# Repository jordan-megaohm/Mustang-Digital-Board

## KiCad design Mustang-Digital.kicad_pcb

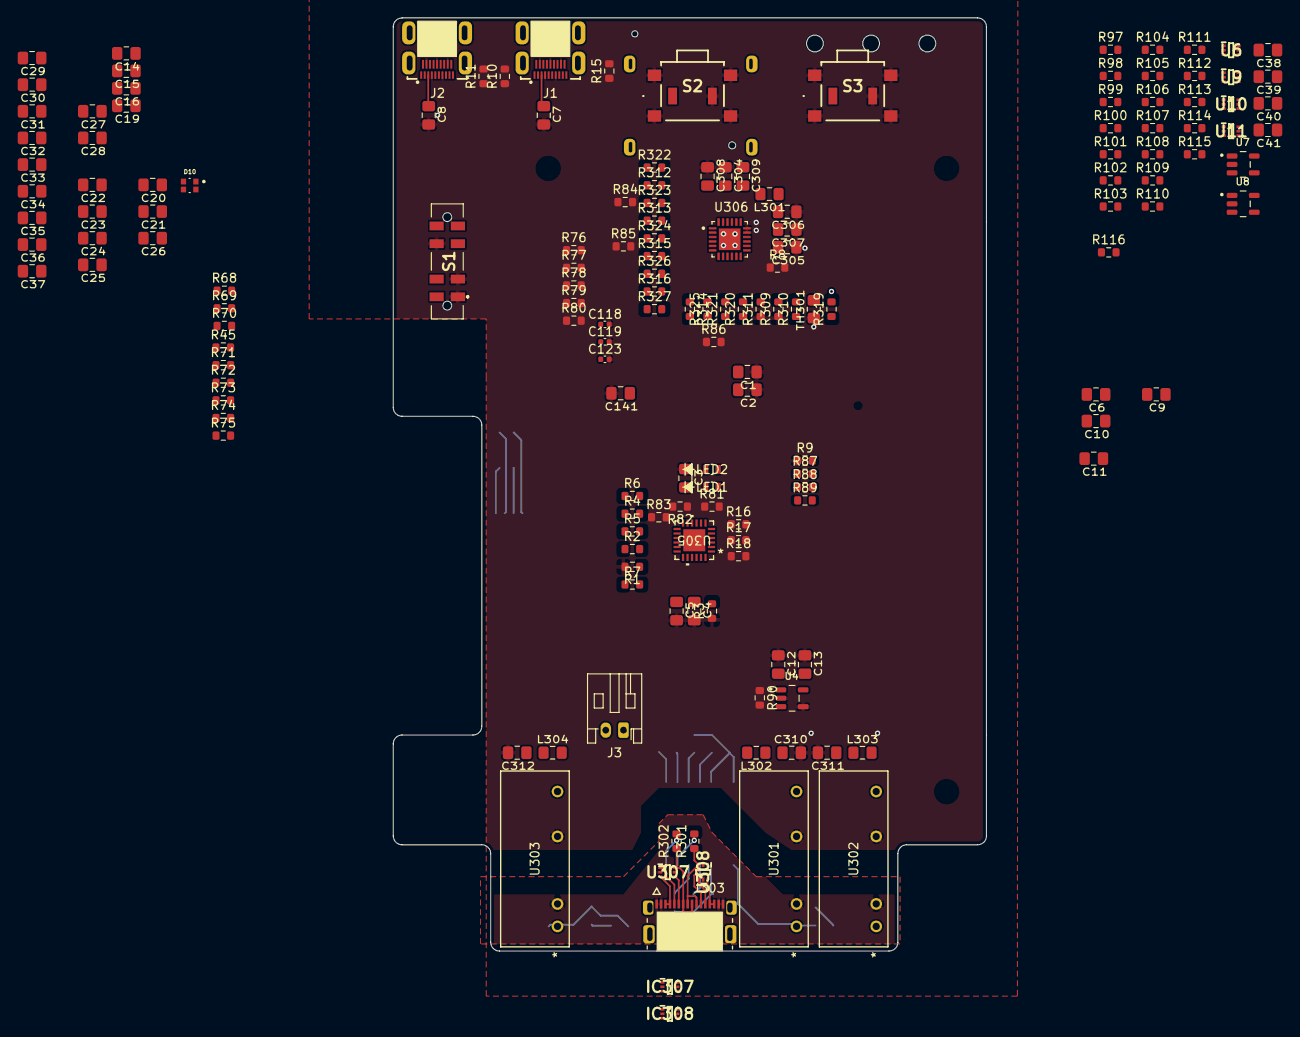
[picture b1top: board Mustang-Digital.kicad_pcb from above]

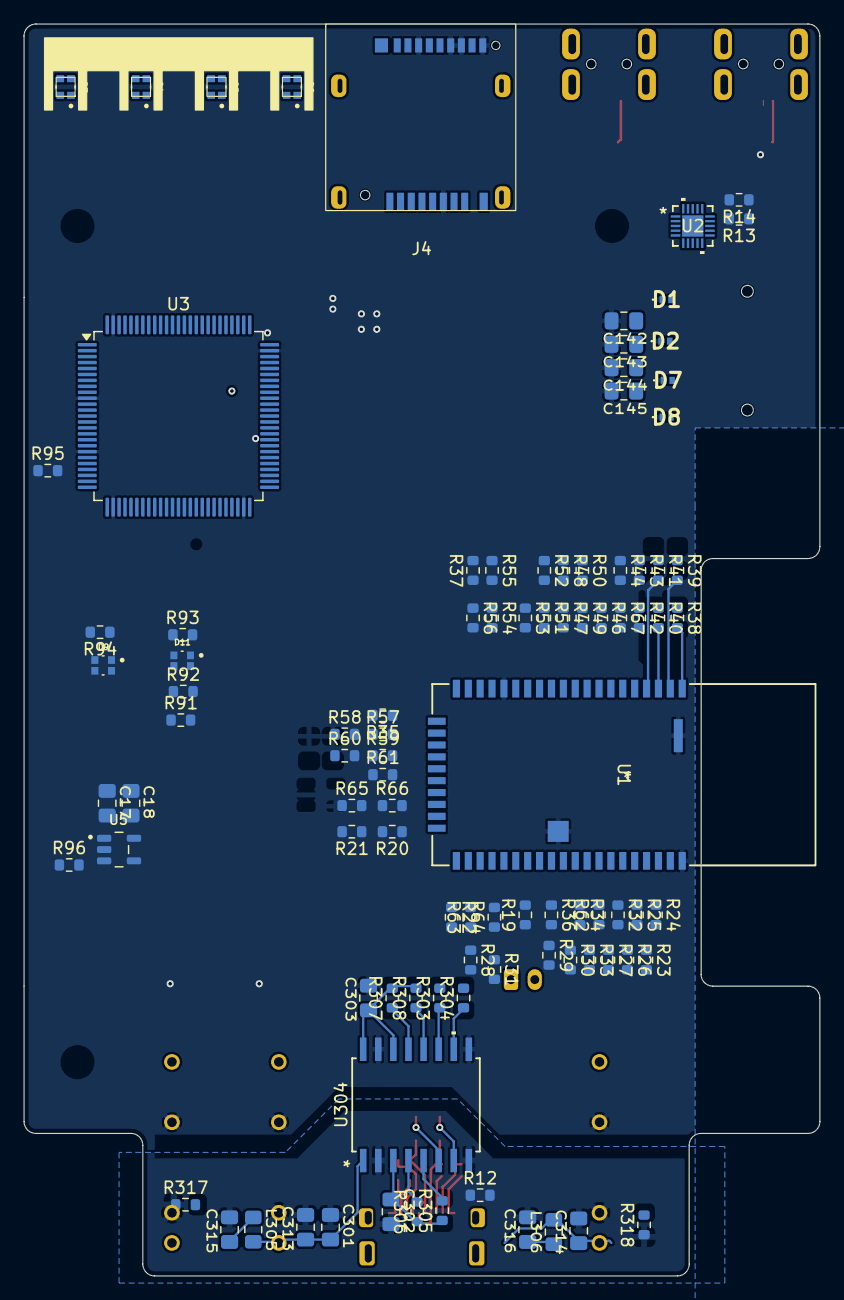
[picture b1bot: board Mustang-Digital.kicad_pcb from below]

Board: 4 copper layers, 67.0 x 105.4 mm, 258 parts (97 on the bottom side), 215 nets.

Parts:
C1, C6, C7, C8, C9, C10, C11, C20, C21, C22, C23, C24, C25, C26, C27, C28, C29, C30, C31, C32, C33, C34, C35, C36, C301, C302, C303, C315, C316: 0.1uF; C_0805_2012Metric_Pad1.18x1.45mm_HandSolder
C2, C3, C12, C13, C17, C18, C37, C38, C39, C40, C41, C143: 1uF; C_0805_2012Metric_Pad1.18x1.45mm_HandSolder
C4, C5: 18pF; C_0805_2012Metric_Pad1.18x1.45mm_HandSolder
C14, C19, C141, C142, C144, C145: .1uF; C_0805_2012Metric_Pad1.18x1.45mm_HandSolder
C15, C16: 10nF; C_0805_2012Metric_Pad1.18x1.45mm_HandSolder
C118: .1uF; C_0402_1005Metric
C119: 10nF; C_0402_1005Metric
C123: 1uF; C_0402_1005Metric
C304, C310, C311, C312, C313, C314: 4.7uF; C_0805_2012Metric_Pad1.18x1.45mm_HandSolder
C305, C306, C307: 10uF; C_0805_2012Metric_Pad1.18x1.45mm_HandSolder
C308: 8.2uF; C_0805_2012Metric_Pad1.18x1.45mm_HandSolder
C309: 47nF; C_0805_2012Metric_Pad1.18x1.45mm_HandSolder
D1, D2, D7, D8: ESD7551N2T5G
D3, D4, D5, D6, D9, D10, D11: EAST1616RGBA3; LED_EAST1616RGBA3
IC307, IC308: TPD4E1B06DRLR; SOTFL50P160X60-6N
J1, J2: 685119248123
J3: Conn_01x02_Pin_JST-PH_Batt; JST_PH_S2B-PH-K_1x02_P2.00mm_Horizontal
J4: Micro_SD_Card_4.0_CUI; microSD_XC_CUI_MSD4-1-A
J303: 2130830005; MOLEX_2130830005
L301, L305, L306: 1uH; L_0805_2012Metric_Pad1.15x1.40mm_HandSolder
L302, L303, L304: 10uH; L_0805_2012Metric_Pad1.15x1.40mm_HandSolder
LED1, LED2: EAST16084BA8; LED_EAST16084BA8_EVE
MECH1: Light_Pipe_LEDs
R1, R2: 100K; R_0603_1608Metric
R3: 12K; R_0603_1608Metric
R4, R5, R6, R7, R16, R17, R18, R19, R20, R21, R22, R23, R24, R25, R26, R27, R28, R29, R30, R31, R32, R33, R34, R35, R36, R37, R38, R39, R40, R41, R42, R47, R48, R54, R55, R56, R60, R61, R62, R70, R81, R82, R83, R90, R96, R97, R98, R99, R100, R101, R102, R103, R104, R105, R106, R107, R108, R109, R110, R111, R112, R113, R114, R115, R301, R302, R303, R304, R319, R320, R321, R322, R323, R324, R325, R326, R327: 24R; R_0603_1608Metric
R8, R9, R10, R11, R12, R13, R14, R15, R43, R44, R46, R49, R50, R51, R52, R53, R57, R58, R59, R63, R64, R65, R66, R67, R68, R69, R87, R88, R89, R95, R116: 0R; R_0603_1608Metric
R45, R72, R77, R79: 1K; R_0603_1608Metric
R71, R73, R74, R75, R78, R80, R94, R305, R306, R307, R308, R312, R313, R314, R315, R316: 10K; R_0603_1608Metric
R76: 2.7K; R_0603_1608Metric
R84, R85, R86, R91, R92, R93, R310, R317, R318: 5.23K; R_0603_1608Metric
R309: 30.9K; R_0603_1608Metric
R311: 249R; R_0603_1608Metric
S1: JS207011JCQNR
S2, S3: PTS645VN13SMTR92LFS
TH301: Thermistor; R_0805_2012Metric_Pad1.20x1.40mm_HandSolder
U1: BM83SM1-00TB; BM83_MCH
U2: LP5012RUKR; QFN_2RUKR_TEX
U3: STM32L496VGT6_Mustang; LQFP-100_14x14mm_P0.5mm
U4, U5, U7: LP5907MFX-3.3_NOPB; SOT95P280X145-5N
U6, U9, U10, U11, U307, U308: TPD4E1B06DRLR; SOTFL50P160X60-6N
U8: LP5907MFX-1.8_NOPB; SOT95P280X145-5N
U301, U302, U303: SPU03L-05; SPU03L-05_MWU
U304: ADUM4160BRWZ; RW_16_ADI
U305: USB2422T-I/MJ; SQFN24_4X4MC_MCH
U306: BQ24296RGER; QFN50P400X400X100-25N

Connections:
+3V3: C1.1, C2.1, C9.1, C13.1, C21.1, C22.1, C23.1, C24.1, C25.1, C31.1, C32.1, C33.1, C34.1, C35.1, D3.3, D4.3, D5.3, D6.3, D10.3, R69.1, R71.2, R73.2, R74.2, R75.2, R78.2, R80.2, R88.2, R89.2, R95.1, U2.16 (VCC), U3.11 (VDD), U3.28 (VDD), U3.50 (VDD), U3.75 (VDD), U3.100 (VDD), U4.5 (OUT), U305.1 (VDD33), U305.9 (VDD33), U305.18 (VDD33)
+5V: C118.1, C119.1, C123.1
/BT/P2_3: R34.2, R93.2
/BT/P2_6: R35.2, R92.2
/BT/P2_7: R36.2, R91.2
/BT/SYS_PWR: C27.1, D9.3, LED1.2, LED2.2, R59.1
/BT/USB_DM: R18.2, U1.36 (DM)
/BT/USB_DP: R19.2, U1.37 (DP)
/Buds/ENABLE_PINS: J1.18 (ENABLE_PINS), J2.18 (ENABLE_PINS)
/Buds/I2C_SCL: J1.11 (I2C_SCL), J2.11 (I2C_SCL)
/Buds/I2C_SDA: J1.9 (I2C_SDA), J2.9 (I2C_SDA)
/Buds/REF: J1.3 (REF), J2.3 (REF)
/Charging_Isolation/VBUS0: IC307.3 (IO2), IC308.6 (IO4)
/Charging_USB/5V: C6.1, C310.2, C311.2, C312.2, L302.2, L303.2, L304.2, R2.1, R57.1, R87.2, U306.1 (VBUS), U306.24 (VBUS)
/Charging_USB/BAT: C305.1, R8.1, R68.1, U306.13 (BAT), U306.14 (BAT)
/Charging_USB/BAT_INT: R86.1, R325.1
/Charging_USB/BAT_PG: R84.1, R323.1
/Charging_USB/BAT_STAT: R85.1, R324.1
/Charging_USB/BTST: C309.1, U306.21 (BTST)
/Charging_USB/CC1: J303.A5 (CC1), R318.1, U307.1 (IO1)
/Charging_USB/CC2: J303.B5 (CC2), R317.2, U308.1 (IO1)
/Charging_USB/CE: R320.2, U306.9 (CE)
/Charging_USB/CRFILT: C3.1, U305.10 (CRFILT)
/Charging_USB/DAB+: J303.A6 (DA+), J303.B6 (DB+), R302.1, U307.6 (IO4)
/Charging_USB/DAB-: J303.A7 (DA-), J303.B7 (DB-), R301.1, U308.3 (IO2)
/Charging_USB/DD+: R304.1, U304.10 (DD+)
/Charging_USB/DD-: R303.1, U304.11 (DD-)
/Charging_USB/DM1: R16.1, U305.2 (USBDM_DN1*PRT_DIS_M1)
/Charging_USB/DM2: R18.1, U305.4 (USBDM_DN2*PRT_DIS_M2)
/Charging_USB/DMU: R303.2, U305.19 (USBDM_UP)
/Charging_USB/DP1: R17.1, U305.3 (USBDP_DN1*PRT_DIS_P1)
/Charging_USB/DP2: R19.1, U305.5 (USBDP_DN2*PRT_DIS_P2)
/Charging_USB/DPU: R304.2, U305.20 (USBDP_UP)
/Charging_USB/ILIM: R311.2, U306.10 (ILIM)
/Charging_USB/INT: R325.2, U306.7 (INT)
/Charging_USB/OCS1_N: R81.1, U305.8 (OCS1_N)
/Charging_USB/OCS2_N: R83.1, U305.12 (OCS2_N)
/Charging_USB/OTG: R321.2, U306.8 (OTG)
/Charging_USB/PDEN: R306.2, U304.4 (PDEN)
/Charging_USB/PG: R323.2, U306.3 (PG)
/Charging_USB/PIN: R308.1, U304.12 (PIN)
/Charging_USB/PMID: C308.1, U306.23 (PMID)
/Charging_USB/PRTPWR1: R70.1, U305.7 (PRTPWR1*(BC_EM1))
/Charging_USB/PRTPWR2: R82.1, U305.11 (PRTPWR2)
/Charging_USB/PSEL: R322.2, U306.2 (PSEL)
/Charging_USB/QON: R319.2, U306.12 (QON)
/Charging_USB/RBIAS: R3.1, U305.24 (RBIAS)
/Charging_USB/REGN: C304.1, R310.1, U306.22 (REGN)
/Charging_USB/RESET_N: R6.2, U305.15 (RESET_N)
/Charging_USB/SBU1: J303.A8 (SBU1), U308.4 (IO3)
/Charging_USB/SBU2: J303.B8 (SBU2), U307.4 (IO3)
/Charging_USB/SCL: R326.2, U306.5 (SCL)
/Charging_USB/SDA: R327.2, U306.6 (SDA)
/Charging_USB/SMBCLK: R4.2, U305.14 (SMBCLK*CFG_SEL0)
/Charging_USB/SMBDATA: R5.2, U305.13 (SMBDATA*NON_REM1)
/Charging_USB/SPD: R307.1, U304.13 (SPD)
/Charging_USB/SPU: R305.2, U304.5 (SPU)
/Charging_USB/STAT: R324.2, U306.4 (STAT)
/Charging_USB/SUSP_IND: R7.2, U305.17 (SUSP_IND*LOCAL_PWR*(NON_REM0))
/Charging_USB/SW: C309.2, L301.1, U306.19 (SW), U306.20 (SW)
/Charging_USB/TS: R309.2, R310.2, TH301.1, U306.11 (TS)
/Charging_USB/UD+: R302.2, U304.7 (UD+)
/Charging_USB/UD-: R301.2, U304.6 (UD-)
/Charging_USB/USB_DM_MCU: R16.2, U3.70 (PA11)
/Charging_USB/USB_DP_MCU: R17.2, U3.71 (PA12)
/Charging_USB/USB_RESET_N: R6.1, R114.2
/Charging_USB/USB_SUSP_IND: R7.1, R115.2
/Charging_USB/VBUS0: C315.2, C316.2, J303.A4 (VBUS1), J303.A9 (VBUS2), J303.B4 (VBUS3), J303.B9 (VBUS4), L305.2, L306.2, U307.3 (IO2), U308.6 (IO4)
/Charging_USB/VBUS1: C301.1, C313.2, C314.2, L305.1, L306.1, U301.1 (VIN+), U302.1 (VIN+), U303.1 (VIN+), U304.1 (VBUS1)
/Charging_USB/VBUS_DET: R1.2, R2.2, U305.16 (VBUS_DET)
/Charging_USB/VDD1: C302.2, R305.1, R306.1, U304.3 (VDD1)
/Charging_USB/VOUT1: L302.1, U301.7 (VOUT+)
/Charging_USB/VOUT2: L303.1, U302.7 (VOUT+)
/Charging_USB/VOUT3: L304.1, U303.7 (VOUT+)
/Charging_USB/VSYS: C7.2, C8.2, C12.1, C17.1, C38.1, C40.1, C306.1, C307.1, J1.5 (VSYS), J2.5 (VSYS), L301.2, R90.1, U4.1 (IN), U5.1 (IN), U7.1 (IN), U8.1 (IN), U306.15 (SYS), U306.16 (SYS)
/Charging_USB/XIN: C4.2, U305.22 (XTALIN*CLKIN)
/Charging_USB/XOUT: C5.2, U305.21 (XTAOUT*(CLKIN_EM))
/LEDs_Switches/LED_SCL: R74.1, U2.18 (SDL)
/LEDs_Switches/LED_SDA: R75.1, U2.17 (SDA)
/LEDs_Switches/SW_BTPAIR: C145.2, D8.2, R79.2
/LEDs_Switches/SW_PLAY: C142.2, D2.2, R72.1
/LEDs_Switches/SW_PWR: C144.2, D7.2, R77.1
/LEDs_Switches/SW_RECORD: C141.2, D1.2, R45.1
/MCU/VBAT: C36.1, U3.6 (VBAT)
/MCU/VUSB: C29.1, U3.73 (VDDUSB)
/SPK_AUDIO+L: J1.1 (SPK_AUDIO+), R46.1
/SPK_AUDIO+R: J2.1 (SPK_AUDIO+), R43.1
/SPK_AUDIO-L: J1.2 (SPK_AUDIO-), R67.1
/SPK_AUDIO-R: J2.2 (SPK_AUDIO-), R44.1
/TALK_MICL: J1.6 (TALK_MIC), R50.1
/TALK_MICR: J2.6 (TALK_MIC), R52.1
GND: C1.2, C2.2, C3.2, C4.1, C5.1, C6.2, C7.1, C8.1, C9.2, C10.2, C11.2, C12.2, C13.2, C14.2, C15.2, C16.2, C17.2, C18.2, C19.2, C20.2, C21.2, C22.2, C23.2, C24.2, C25.2, C26.1, C27.2, C28.2, C29.2, C30.2, C31.2, C32.2, C33.2, C34.2, C35.2, C36.2, C37.2, C38.2, C39.2, C40.2, C41.2, C118.2, C119.2, C123.2, C141.1, C142.1, C143.1, C144.1, C145.1, C303.1, C304.2, C305.2, C306.2, C307.2, C308.2, C310.1, C311.1, C312.1, D1.1, D2.1, D7.1, D8.1, J1.4 (GND), J1.7 (GND), J1.10 (GND), J1.13 (GND), J1.16 (GND), J2.4 (GND), J2.7 (GND), J2.10 (GND), J2.13 (GND), J2.16 (GND), J4.6 (VSS), J4.17 (VSS), J4.20 (VSS), J4.21 (D1-), J4.23 (VSS), R1.1, R3.2, R9.1, R10.1, R11.1, R13.1, R14.1, R15.1, R76.1, R94.2, R101.2, R309.1, R311.1, S1.1 (NO_1), S1.2 (NO_2), S1.7 (NC_3), S2.2 (NO), S2.MP1, S2.MP2, S2.MP3, S2.MP4, S3.2 (NO), S3.MP1, S3.MP2, S3.MP3, S3.MP4, TH301.2, U1.16 (GND), U1.50 (GND), U1.56 (GND), U1.57 (GND), U2.21 (Therm/GND), U3.10 (VSS), U3.19 (VSSA), U3.27 (VSS), U3.49 (VSS), U3.74 (VSS), U3.99 (VSS), U4.2 (GND), U4.4, U5.2 (GND), U5.4, U6.2 (GND), U6.3 (IO2), U6.5 (NC), U7.2 (GND), U7.4, U8.2 (GND), U8.4, U9.2 (GND), U9.5 (NC), U10.2 (GND), U10.5 (NC), U11.2 (GND), U11.5 (NC), U301.5 (VOUT-), U302.5 (VOUT-), U303.5 (VOUT-), U304.9 (GND2), U304.15 (GND2), U305.25 (EPAD), U306.17 (PGND), U306.18 (PGND), U306.25 (PAD)
GNDPWR: C301.2, C302.1, C313.1, C314.1, C315.1, C316.1, IC307.2 (GND), IC307.5 (NC), IC308.2 (GND), IC308.5 (NC), J303.A1 (GND1), J303.A12 (GND2), J303.B1 (GND3), J303.B12 (GND4), R12.1, R317.1, R318.2, U301.2 (VIN-), U302.2 (VIN-), U303.2 (VIN-), U304.2 (GND1), U304.8 (GND1), U307.2 (GND), U307.5 (NC), U308.2 (GND), U308.5 (NC)
unnamed: D9.1, R94.1
unnamed: D9.2, R64.1
unnamed: D9.4, R63.1
unnamed: D10.1, R86.2
unnamed: D10.2, R85.2
unnamed: D10.4, R84.2
unnamed: D11.1, R93.1
unnamed: D11.2, R92.1
unnamed: D11.4, R91.1
unnamed: J1.S1 (SHIELD), J1.S2 (SHIELD), J1.S3 (SHIELD), J1.S4 (SHIELD), R10.2
unnamed: J2.S1 (SHIELD), J2.S2 (SHIELD), J2.S3 (SHIELD), J2.S4 (SHIELD), R11.2
unnamed: C11.1, J3.1 (+Batt), R8.2
unnamed: C10.1, J3.2 (-Batt), R9.2
unnamed: J4.9 (CD), R99.2, U9.3 (IO2)
unnamed: J4.5 (CLK), R107.2, U10.1 (IO1)
unnamed: J4.3 (CMD), R108.1, U10.3 (IO2)
unnamed: J4.18 (D0+), R109.2, U6.6 (IO4)
unnamed: J4.19 (D0-), R110.2, U6.4 (IO3)
unnamed: J4.22 (D1+), R102.2, U6.1 (IO1)
unnamed: J4.7 (DAT0/RCLK+), R103.2, U9.6 (IO4)
unnamed: J4.8 (DAT1/RCLK-), R104.2, U9.4 (IO3)
unnamed: J4.1 (DAT2), R105.2, U10.6 (IO4)
unnamed: J4.2 (DAT3/CD), R106.2, U10.4 (IO3)
unnamed: J4.10 (SHIELD), J4.11 (SHIELD), J4.12 (SHIELD), J4.13 (SHIELD), J4.14 (SHIELD), R15.2
unnamed: J4.16 (SWIO), R100.2, U9.1 (IO1)
unnamed: C41.1, J4.15 (VDD_1.8), U8.5 (OUT), U11.1 (IO1)
unnamed: C39.1, J4.4 (VDD_3.3), U7.5 (OUT), U11.3 (IO2)
unnamed: J303.SH1 (SHIELD1), J303.SH2 (SHIELD2), J303.SH3 (SHIELD3), J303.SH4 (SHIELD4), R12.2
unnamed: R77.2, R78.1, S1.3 (NC_1)
unnamed: R79.1, R80.1, S1.5 (NO_3)
unnamed: R72.2, R73.1, S2.1 (COM)
unnamed: R45.2, R71.1, S3.1 (COM)
unnamed: C19.1, R57.2, U1.22 (ADAP_IN)
unnamed: R48.2, U1.12 (AIL)
unnamed: R47.2, U1.11 (AIR)
unnamed: R46.2, U1.8 (AOHPL)
unnamed: R44.2, R67.2, U1.7 (AOHPM)
unnamed: R43.2, U1.6 (AOHPR)
unnamed: C14.1, R58.2, U1.23 (BAT_IN)
unnamed: R56.2, U1.19 (DMIC1_L)
unnamed: R55.2, U1.18 (DMIC1_R)
unnamed: R54.2, U1.17 (DMIC_CLK)
unnamed: R38.2, U1.1 (DR1)
unnamed: R41.2, U1.4 (DT1)
unnamed: LED2.1, R63.2, U1.32 (LED1)
unnamed: LED1.1, R64.2, U1.34 (LED2)
unnamed: R42.2, U1.5 (MCLK1)
unnamed: R53.2, U1.15 (MICBIAS)
unnamed: R51.2, U1.13 (MICN1)
unnamed: R49.2, U1.9 (MICN2)
unnamed: R52.2, U1.14 (MICP1)
unnamed: R50.2, U1.10 (MICP2)
unnamed: R24.1, U1.49 (P0_0/UART_TX_IND)
unnamed: R27.1, U1.44 (P0_1)
unnamed: R28.1, U1.33 (P0_2)
unnamed: R29.1, U1.38 (P0_3)
unnamed: R30.1, U1.40 (P0_5)
unnamed: R31.1, U1.35 (P0_6)
unnamed: R32.1, U1.45 (P0_7)
unnamed: R26.1, U1.46 (P1_2/TDI_CPU/SCL)
unnamed: R25.1, U1.47 (P1_3/TCK_CPU/SDA)
unnamed: R33.1, U1.41 (P1_6/PWM1)
unnamed: R34.1, U1.42 (P2_3)
unnamed: R35.1, U1.21 (P2_6)
unnamed: R36.1, U1.39 (P2_7)
unnamed: R37.1, U1.20 (P3_2)
unnamed: R22.1, U1.31 (P3_4/UART_RTS)
unnamed: R23.1, U1.48 (P3_7/UART_CTS)
unnamed: R20.1, U1.30 (P8_5/UART_TXD)
unnamed: R21.1, U1.29 (P8_6/UART_RXD)
unnamed: R61.2, U1.26 (PWR(MFB))
unnamed: R39.2, U1.2 (RFS1)
unnamed: R62.2, U1.43 (RST_N)
unnamed: R40.2, U1.3 (SCLK1)
unnamed: C16.1, R66.2, U1.28 (SK2_KEY_AD)
unnamed: C15.1, R65.2, U1.27 (SKI_AMB_DET)
unnamed: R59.2, U1.24 (SYS_PWR)
unnamed: R60.2, U1.25 (VDD_IO)
unnamed: R13.2, U2.14 (ADDR0)
unnamed: R14.2, U2.15 (ADDR1)
unnamed: R76.2, U2.20 (IREF)
unnamed: D3.4, U2.2 (OUT0)
unnamed: D3.2, U2.3 (OUT1)
unnamed: D3.1, U2.4 (OUT2)
unnamed: D4.4, U2.5 (OUT3)
unnamed: D4.2, U2.6 (OUT4)
unnamed: D4.1, U2.7 (OUT5)
unnamed: D5.4, U2.8 (OUT6)
unnamed: D5.2, U2.9 (OUT7)
unnamed: D5.1, U2.10 (OUT8)
unnamed: D6.4, U2.11 (OUT9)
unnamed: D6.2, U2.12 (OUT10)
unnamed: D6.1, U2.13 (OUT11)
unnamed: C143.2, U2.1 (VCAP)
unnamed: R115.1, U3.67 (PA8)
unnamed: R114.1, U3.68 (PA9)
unnamed: R111.1, U3.69 (PA10)
unnamed: R112.1, U3.72 (PA13)
unnamed: R113.1, U3.76 (PA14)
unnamed: R109.1, U3.95 (PB8)
unnamed: R110.1, U3.96 (PB9)
unnamed: R97.1, U3.17 (PC2)
unnamed: R98.1, U3.18 (PC3)
unnamed: R99.1, U3.33 (PC4)
unnamed: R100.1, U3.34 (PC5)
unnamed: R101.1, U3.63 (PC6)
unnamed: R102.1, U3.64 (PC7)
unnamed: R103.1, U3.65 (PC8)
unnamed: R104.1, U3.66 (PC9)
unnamed: R105.1, U3.78 (PC10)
unnamed: R106.1, U3.79 (PC11)
unnamed: R107.1, U3.80 (PC12)
unnamed: R108.2, U3.83 (PD2)
unnamed: C30.1, C37.1, R95.2, U3.22 (VDDA)
unnamed: R90.2, U4.3 (EN)
unnamed: R96.2, U5.3 (EN)
unnamed: C18.1, C28.1, D11.3, R58.1, R68.2, R69.2, U5.5 (OUT)
unnamed: R97.2, U7.3 (EN)
unnamed: R98.2, U8.3 (EN)
unnamed: C26.2, R87.1, R88.1, U304.16 (VBUS2)
unnamed: C303.2, R89.1, R307.2, R308.2, U304.14 (VDD2)
unnamed: C20.1, U305.23 (PLLFILT)

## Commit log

2024-07-12 Import project
2024-07-15 3D models.
2024-07-18 Place and align PCB components to enclosure DXF. Expand PCB 15mm both sides of USB-C. Move BM83 to right side. Cutout PCB along right side for antenna function.
2024-07-19 Footprint inspections and cleanups.
2024-07-29 Add extra mounting hole. Relocate BM83 per Juan.
2024-08-01 Electrical Rules Check fixes in progress.
2024-08-01 Export STEP.
2024-08-09 Use all YAGEO 0603 resistors.
